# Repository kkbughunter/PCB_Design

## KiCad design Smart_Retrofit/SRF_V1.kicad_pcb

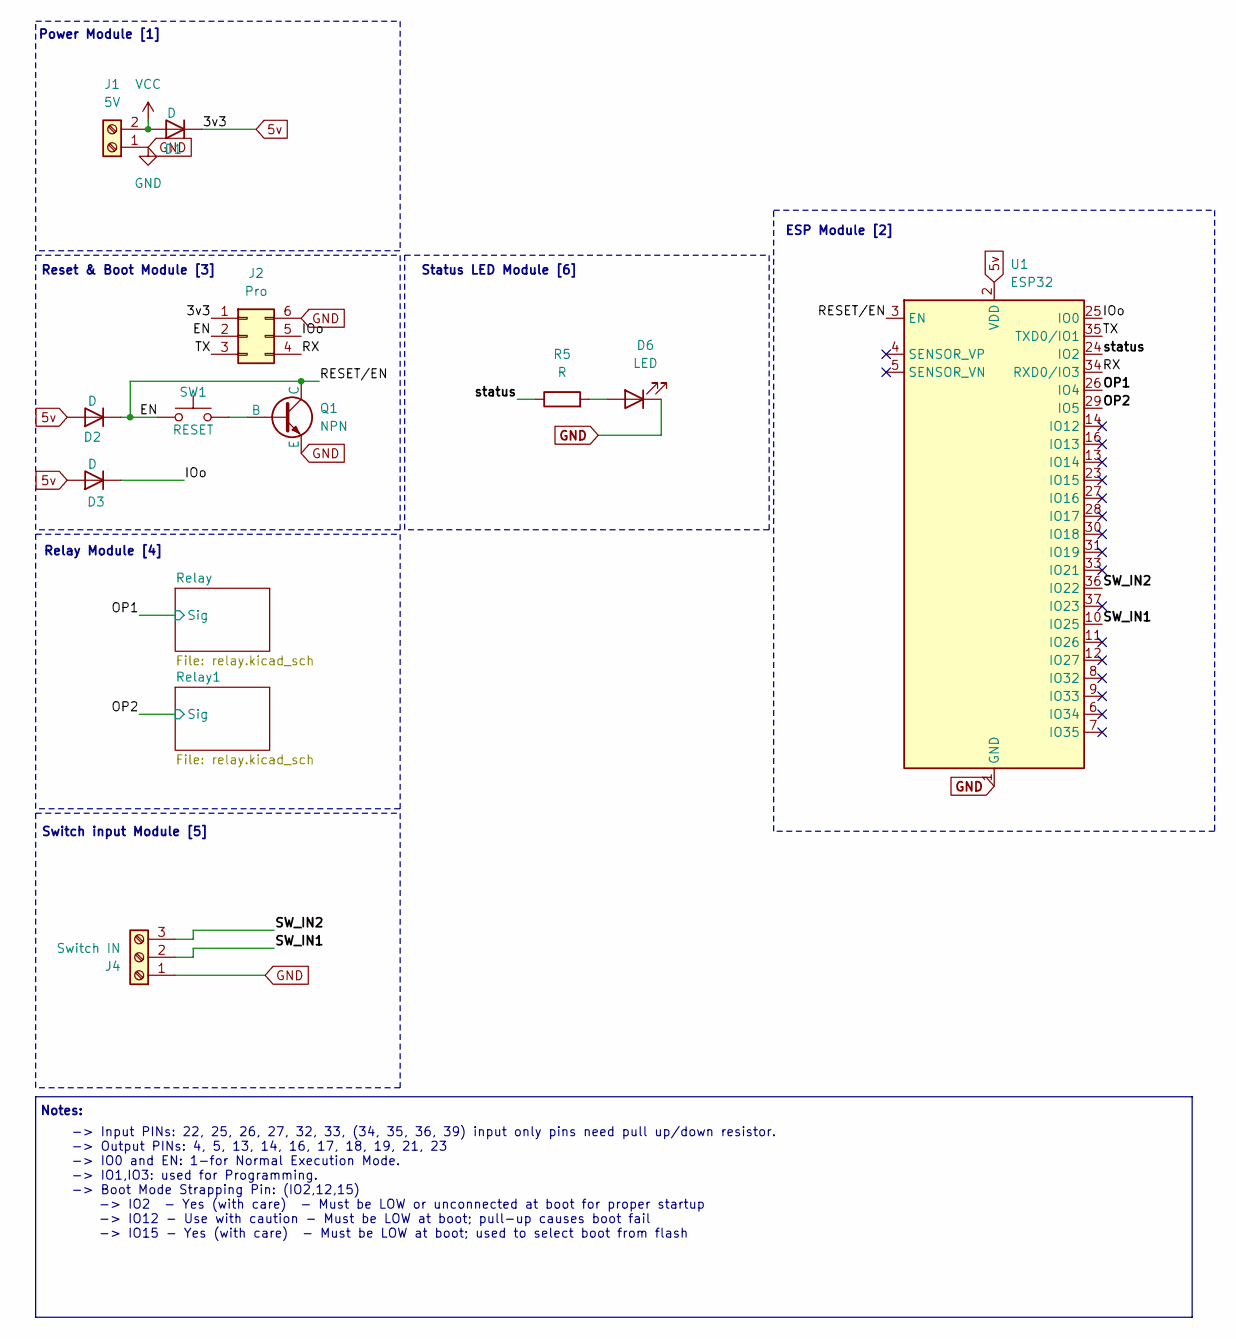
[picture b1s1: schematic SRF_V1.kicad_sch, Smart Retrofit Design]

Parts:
D1, D2, D3: D; D_A-405_P7.62mm_Horizontal
D6: LED; LED_D3.0mm
J1: 5V; TerminalBlock_Phoenix_MPT-0,5-2-2.54_1x02_P2.54mm_Horizontal
J2: Pro; PinHeader_2x03_P2.54mm_Vertical
J4: Switch IN; TerminalBlock_Phoenix_MPT-0,5-3-2.54_1x03_P2.54mm_Horizontal
Q1: NPN; TO-92L_Inline
R5: R; R_Axial_DIN0207_L6.3mm_D2.5mm_P7.62mm_Horizontal
SW1: RESET; SW_PUSH_6mm_H5mm
U1: ESP32; ESP32-WROOM-32D

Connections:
5v: D1.1 (K), D2.2 (A), D3.2 (A), J2.1, U1.2 (VDD); also elsewhere on the board
/EN: D2.1 (K), J2.2, Q1.1 (C), SW1.1, U1.3 (EN)
/IOo: D3.1 (K), J2.5, U1.25 (IO0)
/OP1: U1.26 (IO4); also elsewhere on the board
/OP2: U1.29 (IO5); also elsewhere on the board
/RX: J2.4, U1.34 (RXD0/IO3)
/SW_IN1: J4.2, U1.10 (IO25)
/SW_IN2: J4.3, U1.36 (IO22)
/TX: J2.3, U1.35 (TXD0/IO1)
/status: R5.1, U1.24 (IO2)
GND: D6.1 (K), J1.1, J2.6, J4.1, Q1.3 (E), U1.1 (GND), U1.15 (GND), U1.38 (GND), U1.39 (GND); also elsewhere on the board
unnamed: D6.2 (A), R5.2
unnamed: Q1.2 (B), SW1.2
VCC: D1.2 (A), J1.2

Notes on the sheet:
Notes:
Relay Module [4]
Status LED Module [6]
Power Module [1]
Switch input Module [5]
-> Input PINs: 22, 25, 26, 27, 32, 33, (34, 35, 36, 39) input only pins need pull up/down resistor. -> Output PINs: 4, 5, 13, 14, 16, 17, 18, 19, 21, 23 -> IO0 and EN: 1-for Normal Execution Mode. -> IO1,IO3: used for Programming. -> Boot Mode Strapping Pin: (IO2,12,15) -> IO2 - Yes (with care) - M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
Reset & Boot Module [3]
ESP Module [2]

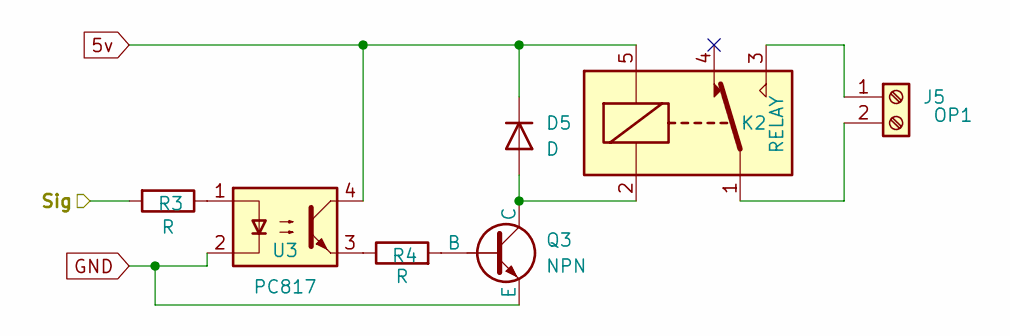
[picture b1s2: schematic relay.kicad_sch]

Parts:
D5: D; D_A-405_P7.62mm_Horizontal
J5: OP1; TerminalBlock_Phoenix_MKDS-1,5-2-5.08_1x02_P5.08mm_Horizont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
K2: RELAY; Relay_SPDT_SANYOU_SRD_Series_Form_C
Q3: NPN; TO-92L_Inline
R3, R4: R; R_Axial_DIN0207_L6.3mm_D2.5mm_P7.62mm_Horizontal
U3: PC817; DIP-4_W7.62mm

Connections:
5v: D5.1 (K), K2.5, U3.4; also elsewhere on the board
/OP2: R3.2; also elsewhere on the board
GND: Q3.3 (E), U3.2; also elsewhere on the board
unnamed: D5.2 (A), K2.2, Q3.1 (C)
unnamed: J5.1, K2.3
unnamed: J5.2, K2.1
unnamed: Q3.2 (B), R4.2
unnamed: R3.1, U3.1
unnamed: R4.1, U3.3

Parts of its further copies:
D4: D; D_A-405_P7.62mm_Horizontal
J3: OP1; TerminalBlock_Phoenix_MKDS-1,5-2-5.08_1x02_P5.08mm_Horizont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
K1: RELAY; Relay_SPDT_SANYOU_SRD_Series_Form_C
Q2: NPN; TO-92L_Inline
R1, R2: R; R_Axial_DIN0207_L6.3mm_D2.5mm_P7.62mm_Horizontal
U2: PC817; DIP-4_W7.62mm

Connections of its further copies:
5v: D4.1 (K), K1.5, U2.4; also elsewhere on the board
/OP1: R1.2; also elsewhere on the board
GND: Q2.3 (E), U2.2; also elsewhere on the board
unnamed: D4.2 (A), K1.2, Q2.1 (C)
unnamed: J3.1, K1.3
unnamed: J3.2, K1.1
unnamed: Q2.2 (B), R2.2
unnamed: R1.1, U2.1
unnamed: R2.1, U2.3

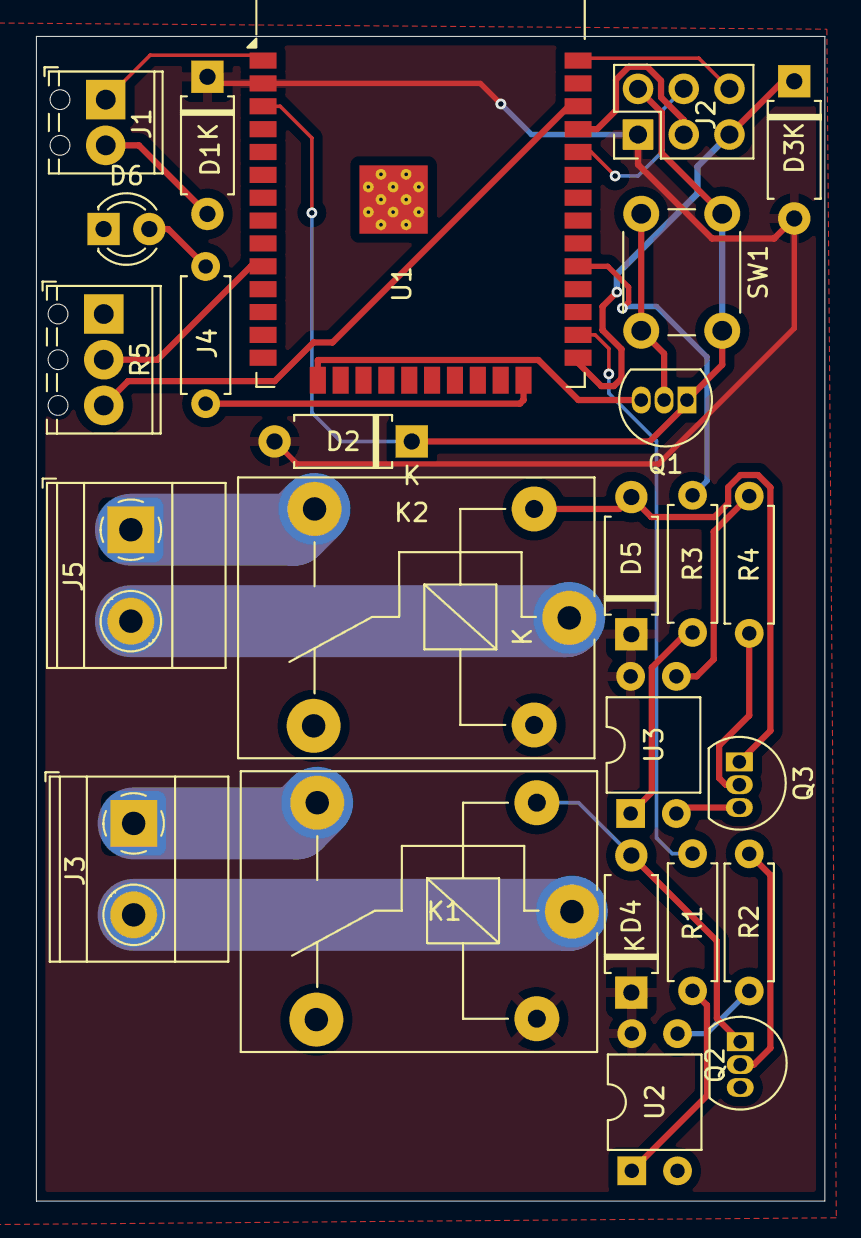
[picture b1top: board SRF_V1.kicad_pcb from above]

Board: 2 copper layers, 43.8 x 64.7 mm, 25 parts (0 on the bottom side), 26 nets.

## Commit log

2025-07-20 Smart Retrofit Project Version 1.0
